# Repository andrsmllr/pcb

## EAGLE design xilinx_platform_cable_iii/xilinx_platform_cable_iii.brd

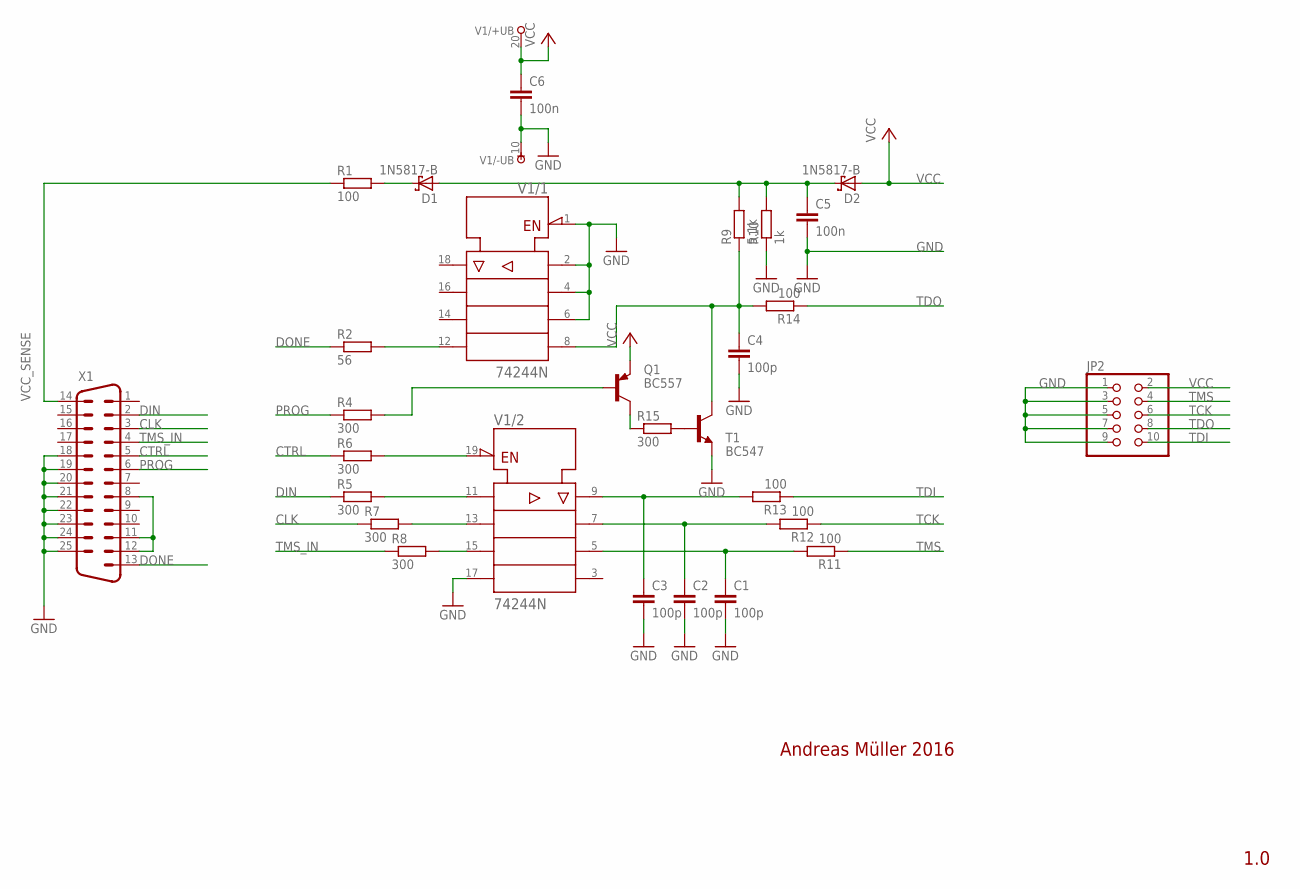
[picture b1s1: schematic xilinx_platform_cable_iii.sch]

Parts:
C1, C2, C3, C4: 100p; C025-030X050
C5, C6: 100n; C025-030X050
D1, D2: 1N5817-B; DO41-7.6
JP2: PINHD-2X5; 2X05
Q1: BC557; TO92
R1, R11, R12, R13, R14: 100; 0207/12
R2: 56; 0207/12
R4, R5, R6, R7, R8, R15: 300; 0207/12
R9: 5.1k; 0207/12
R10: 1k; 0207/12
T1: BC547; TO92
V1: 74244N; DIL20
X1: DB25HP; M25HP

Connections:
CLK: R7.1, X1.3
CTRL: R6.1, X1.5
DIN: R5.1, X1.2
DONE: R2.1, X1.13
GND: C1.2, C2.2, C3.2, C4.2, C5.2, C6.2, JP2.1, JP2.3, JP2.5, JP2.7, JP2.9, R10.1, T1.1 (E), V1.1 (!G), V1.2 (A1), V1.4 (A2), V1.6 (A3), V1.10 (-UB), V1.17 (A4), X1.18, X1.19, X1.20, X1.21, X1.22, X1.23, X1.24, X1.25
unnamed: Q1.3 (C), R15.1
unnamed: R15.2, T1.2 (B)
unnamed: X1.8, X1.11, X1.12
unnamed: Q1.2 (B), R4.2
unnamed: D1.C, R1.2
unnamed: R2.2, V1.12 (Y4)
unnamed: R6.2, V1.19 (!G)
unnamed: R7.2, V1.13 (A2)
unnamed: R8.2, V1.15 (A3)
unnamed: R5.2, V1.11 (A1)
unnamed: C5.1, D1.A, D2.C, R9.2, R10.2
unnamed: C3.1, R13.2, V1.9 (Y1)
unnamed: C2.1, R12.2, V1.7 (Y2)
unnamed: C1.1, R11.2, V1.5 (Y3)
unnamed: C4.1, R9.1, R14.2, T1.3 (C), V1.8 (A4)
PROG: R4.1, X1.6
TCK: JP2.6, R12.1
TDI: JP2.10, R13.1
TDO: JP2.8, R14.1
TMS: JP2.4, R11.1
TMS_IN: R8.1, X1.4
VCC: C6.1, D2.A, JP2.2, Q1.1 (E), V1.20 (+UB)
VCC_SENSE: R1.1, X1.14

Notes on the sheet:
1.0
Andreas Müller 2016

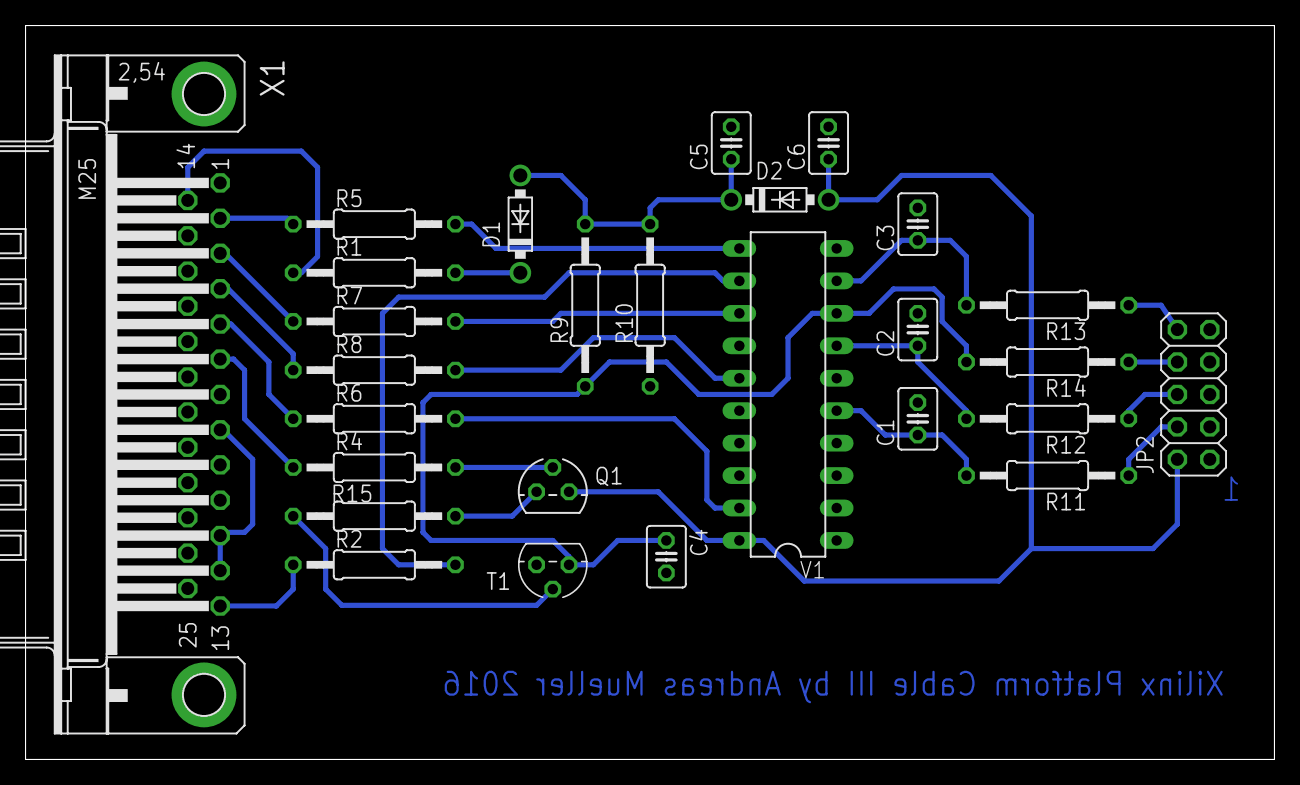
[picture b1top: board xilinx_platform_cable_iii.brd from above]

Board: 2 copper layers, 97.8 x 57.5 mm, 27 parts (0 on the bottom side), 28 nets.

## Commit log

2016-07-30 New project for Xilinx Platform Cable III
2016-08-13 New project for Xilinx CPLD demo board (KiCad)
2016-10-09 Update schematic and layout
2017-05-11 Update schematics and layouts (pin progress)
2017-11-15 Commit current progress (unknown changes).
2017-11-17 Initial commit for 7400_lowend_pwm (draft).
2017-11-17 Initial commmit of fan_rot_sense_disp (draft).
2017-12-14 Update progress
2018-03-27 Update layout, increase via size and improve routing around vias.

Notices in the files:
parts and their libraries:
SparkFun-Connectors: Licensing: CC v3.0 Share-Alike You are welcome to use this library for commercial purposes.
